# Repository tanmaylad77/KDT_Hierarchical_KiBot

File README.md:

<h1 align="center">LE_BMS_A_V2</h1>

<p align="center" width="100%">
  
</p>

***

<p align="center">
  
&nbsp; &nbsp; &nbsp; &nbsp;
  
</p>

***

## SPECIFICATIONS

| Parameter | Value | 
| --- | --- |
| Dimensions | 80.0 × 80.0 mm |

***

## DIRECTORY STRUCTURE

    .
    ├─ Computations       # Misc calculations
    ├─ HTML               # HTML files for generated webpage
    ├─ Images             # Pictures and renders
    │
    ├─ kibot_resources    # External resources for KiBot
    │  ├─ colors          # Color theme for KiCad
    │  ├─ fonts           # Fonts used in the project
    │  ├─ scripts         # External scripts used with KiBot
    │  └─ templates       # Templates for KiBot generated reports
    │
    ├─ kibot_yaml         # KiBot YAML config files
    ├─ KiRI               # KiRI (PCB diff viewer) files
    │
    ├─ lib                # KiCad footprint and symbol libraries
    │  ├─ 3d_models       # Component 3D models
    │  ├─ lib_fp          # Footprint libraries
    │  └─ lib_sym         # Symbol libraries
    │
    ├─ Logos              # Logos
    │
    ├─ Manufacturing      # Assembly and fabrication documents
    │  ├─ Assembly        # Assembly documents (BoM, pos, notes)
    │  │
    │  └─ Fabrication     # Fabrication documents (ZIP, notes)
    │     ├─ Drill Tables # CSV drill tables
    │     └─ Gerbers      # Gerbers
    │
    ├─ Report             # Reports for ERC/DRC
    ├─ Schematic          # PDF of schematic
    ├─ Templates          # Title block templates
    ├─ Testing
    │  └─ Testpoints      # Testpoints tables      
    │
    └─ Variants           # Outputs for assembly variants

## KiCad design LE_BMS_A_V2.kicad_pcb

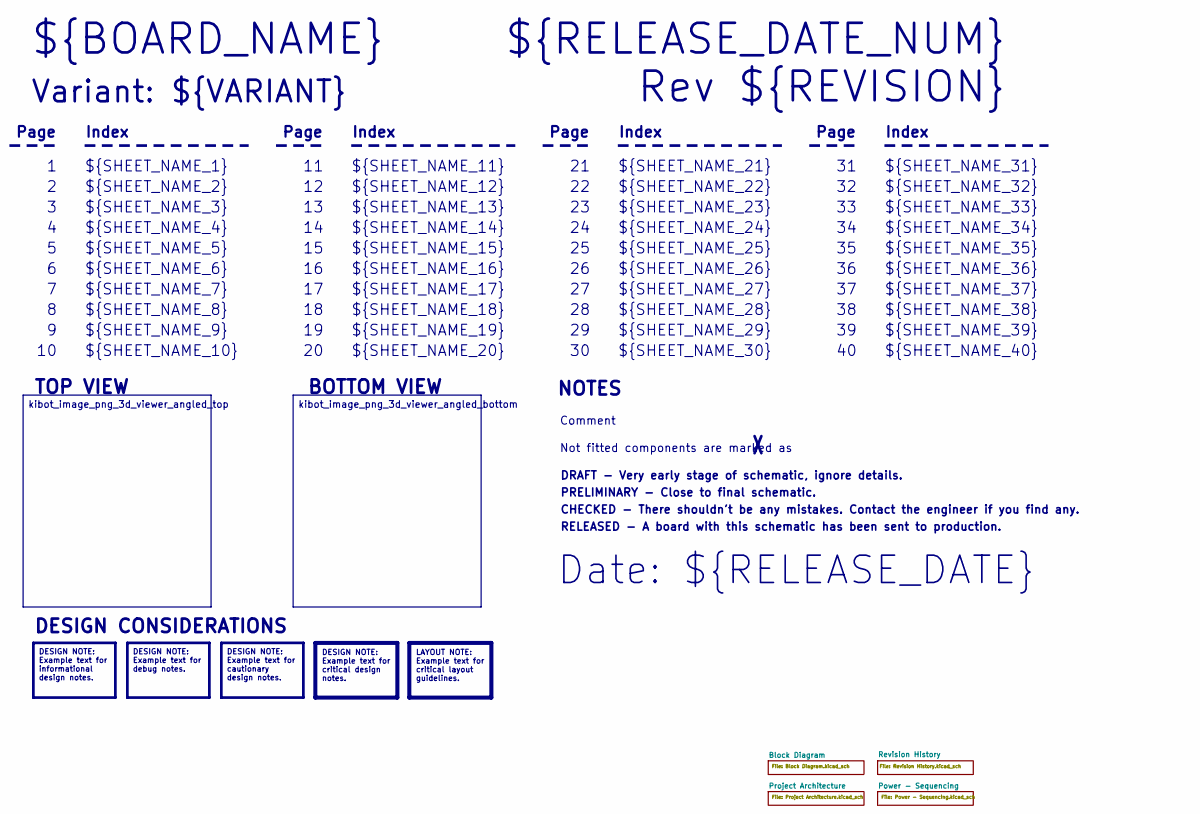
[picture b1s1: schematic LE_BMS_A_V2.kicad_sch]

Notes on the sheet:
Variant: ${VARIANT}
RELEASED - A board with this schematic has been sent to production.
${SHEET_NAME_24}
Index
Page
PRELIMINARY - Close to final schematic.
${SHEET_NAME_22}
DRAFT - Very early stage of schematic, ignore details.
${SHEET_NAME_12}
${SHEET_NAME_8}
${SHEET_NAME_2}
${SHEET_NAME_5}
${SHEET_NAME_20}
${SHEET_NAME_23}
${RELEASE_DATE_NUM}
${SHEET_NAME_35}
Not fitted components are marked as
${SHEET_NAME_11}
${SHEET_NAME_6}
${SHEET_NAME_37}
${SHEET_NAME_26}
${SHEET_NAME_36}
Rev ${REVISION}
${SHEET_NAME_15}
CHECKED - There shouldn't be any mistakes. Contact the engineer if you find any.
BOTTOM VIEW
${SHEET_NAME_14}
${SHEET_NAME_21}
${SHEET_NAME_17}
${SHEET_NAME_18}
Date: ${RELEASE_DATE}
${SHEET_NAME_7}
${SHEET_NAME_31}
${BOARD_NAME}
NOTES
${SHEET_NAME_40}
${SHEET_NAME_39}
${SHEET_NAME_32}
${SHEET_NAME_1}
${SHEET_NAME_9}

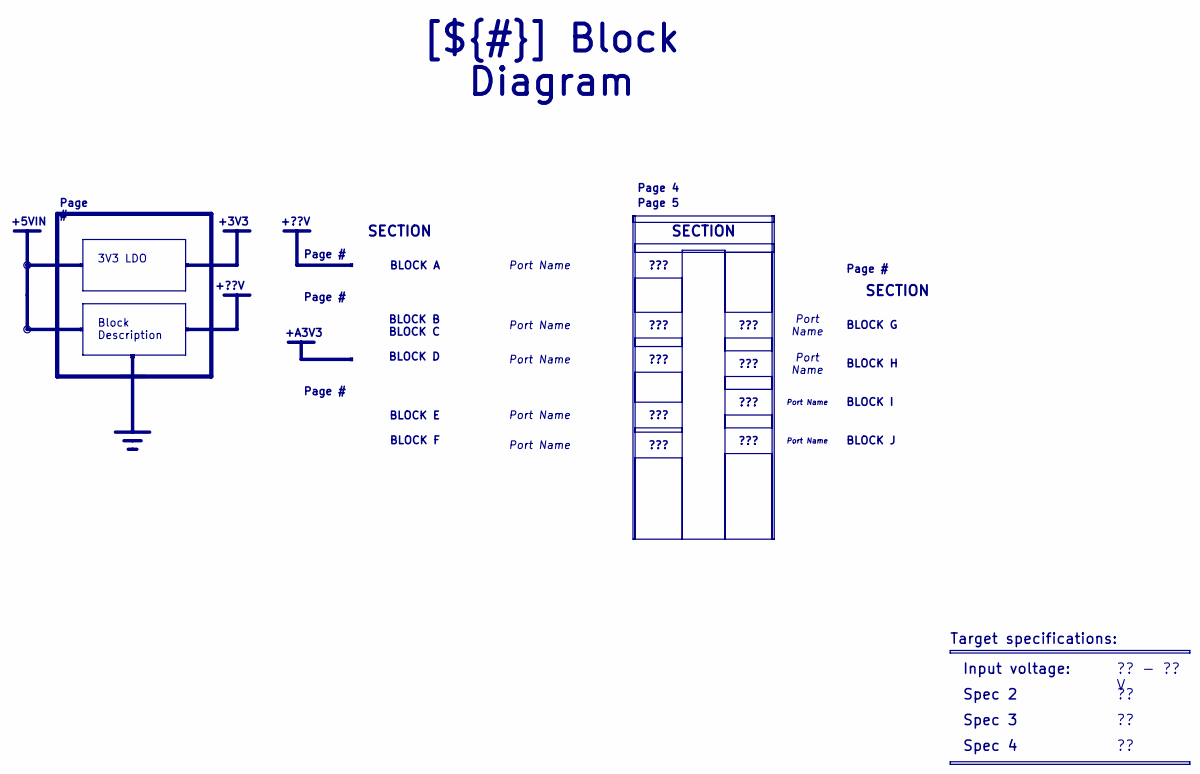
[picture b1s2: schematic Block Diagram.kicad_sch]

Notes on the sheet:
+5VIN
+??V
+A3V3
+3V3
SECTION
Spec 4
BLOCK H
BLOCK B BLOCK C BLOCK D
BLOCK I
?? - ?? V
3V3 LDO
???
Port Name
BLOCK G
Page #
Page 4
[${#}] ${TITLE}
Input voltage:
Target specifications:
Spec 3
Spec 2
Block Description
BLOCK A
BLOCK E BLOCK F
BLOCK J
Page 5

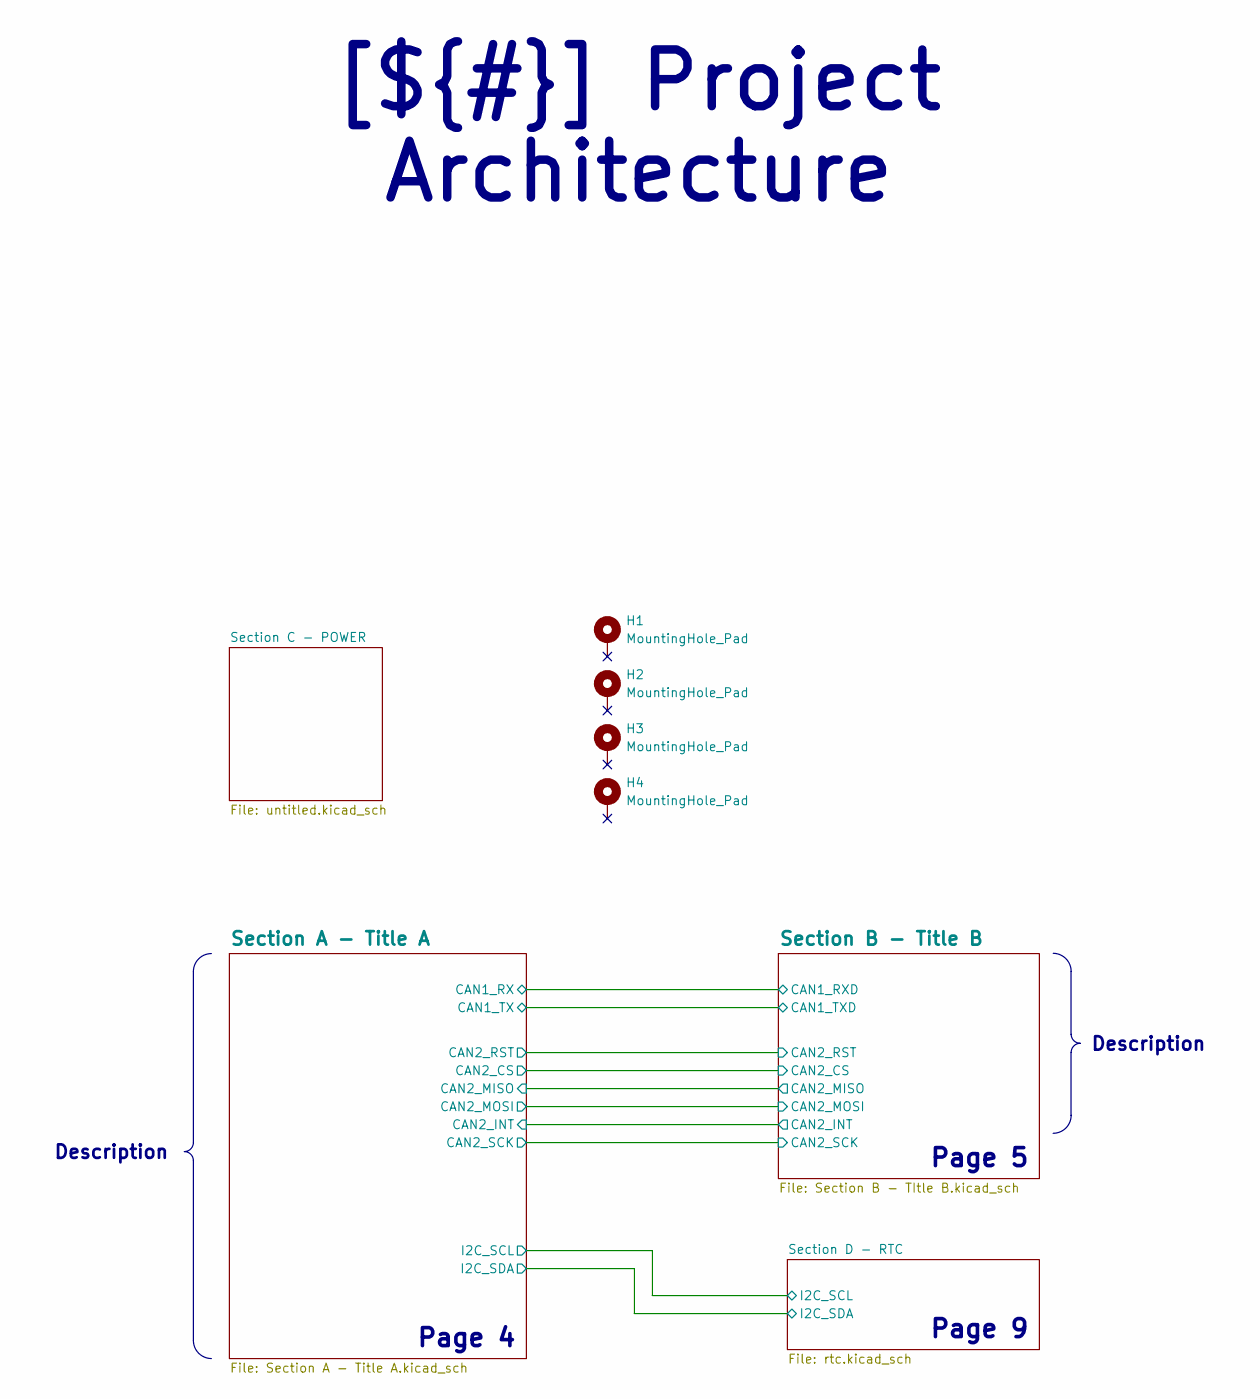
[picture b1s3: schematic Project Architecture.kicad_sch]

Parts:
H1, H2, H3, H4: MountingHole_Pad; MountingHole_3.2mm_M3_DIN965_Pad

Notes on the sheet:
Page 9
Page 5
Page 4
Description
[${#}] ${TITLE}

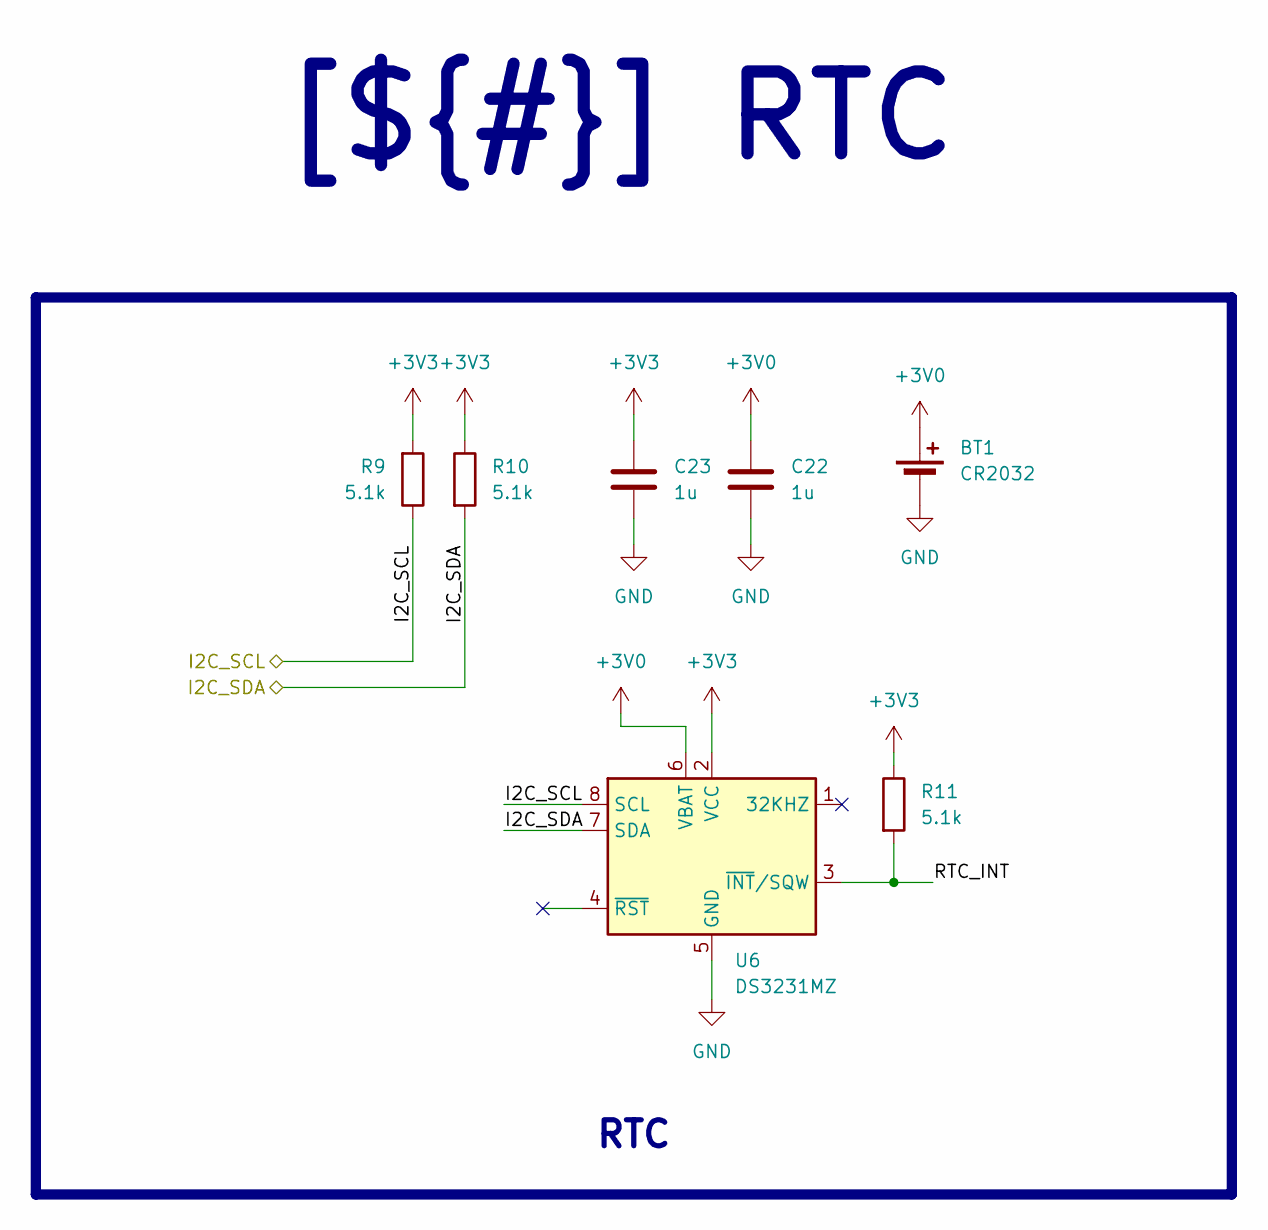
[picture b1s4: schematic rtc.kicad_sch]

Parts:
BT1: CR2032; BatteryHolder_MYOUNG_BS-07-A1BJ001_CR2032
C22, C23: 1u; C_0603_1608Metric_Pad1.08x0.95mm_HandSolder
R9, R10, R11: 5.1k; R_0603_1608Metric_Pad0.98x0.95mm_HandSolder
U6: DS3231MZ; SOIC-8_3.9x4.9mm_P1.27mm

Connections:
+3V0: BT1.1 (+), C22.1, U6.6 (VBAT)
+3V3: C23.1, R9.2, R10.1, R11.1, U6.2 (VCC); also elsewhere on the board
/Project Architecture/Section D - RTC/I2C_SCL: R9.1, U6.8 (SCL); also elsewhere on the board
/Project Architecture/Section D - RTC/I2C_SDA: R10.2, U6.7 (SDA); also elsewhere on the board
/Project Architecture/Section D - RTC/RTC_INT: R11.2, U6.3 (~INT/SQW)
GND: BT1.2 (-), C22.2, C23.2, U6.5 (GND); also elsewhere on the board

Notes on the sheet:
[${#}] ${TITLE}
RTC

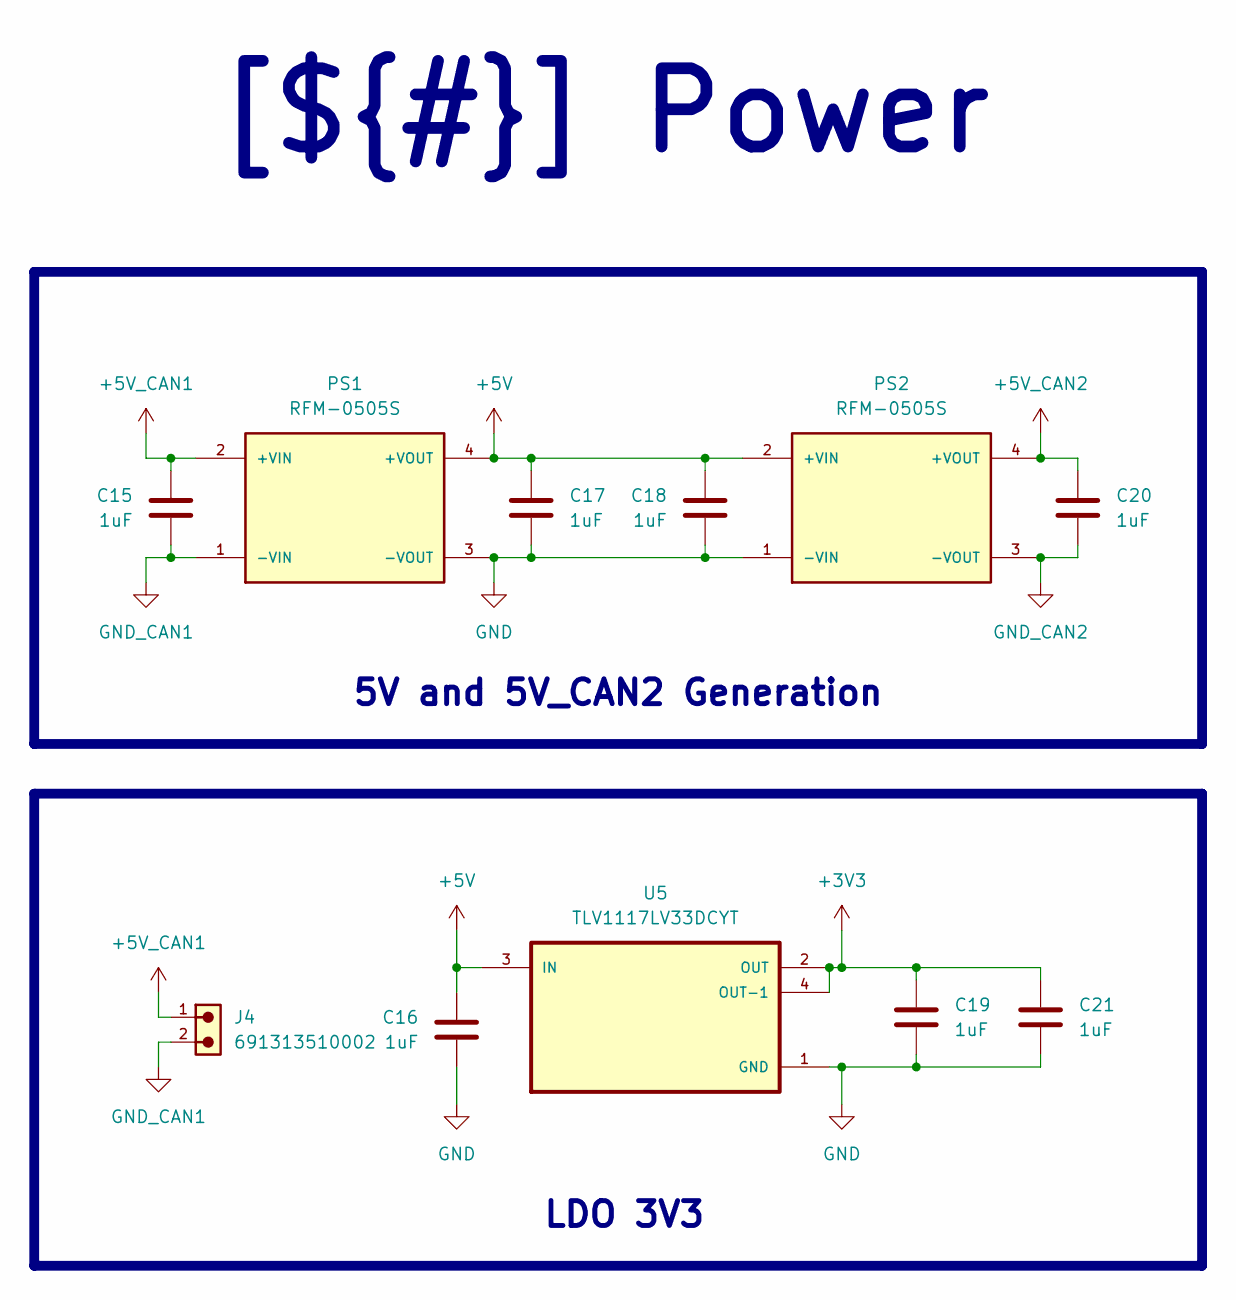
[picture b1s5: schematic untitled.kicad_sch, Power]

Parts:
C15, C16, C17, C18, C19, C20, C21: 1uF; C_0603_1608Metric_Pad1.08x0.95mm_HandSolder
J4: 691313510002
PS1, PS2: RFM-0505S; CONV_RFM-0505S; PARTREV 0
U5: TLV1117LV33DCYT; SOT230P700X180-4N

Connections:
+3V3: C19.1, C21.1, U5.2 (OUT), U5.4 (OUT-1); also elsewhere on the board
+5V: C16.1, C17.1, C18.1, PS1.4 (+VOUT), PS2.2 (+VIN), U5.3 (IN); also elsewhere on the board
+5V_CAN1: C15.1, J4.1, PS1.2 (+VIN); also elsewhere on the board
+5V_CAN2: C20.1, PS2.4 (+VOUT); also elsewhere on the board
GND: C16.2, C17.2, C18.2, C19.2, C21.2, PS1.3 (-VOUT), PS2.1 (-VIN), U5.1 (GND); also elsewhere on the board
GND_CAN1: C15.2, J4.2, PS1.1 (-VIN); also elsewhere on the board
GND_CAN2: C20.2, PS2.3 (-VOUT); also elsewhere on the board

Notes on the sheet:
[${#}] ${TITLE}
5V and 5V_CAN2 Generation
LDO 3V3

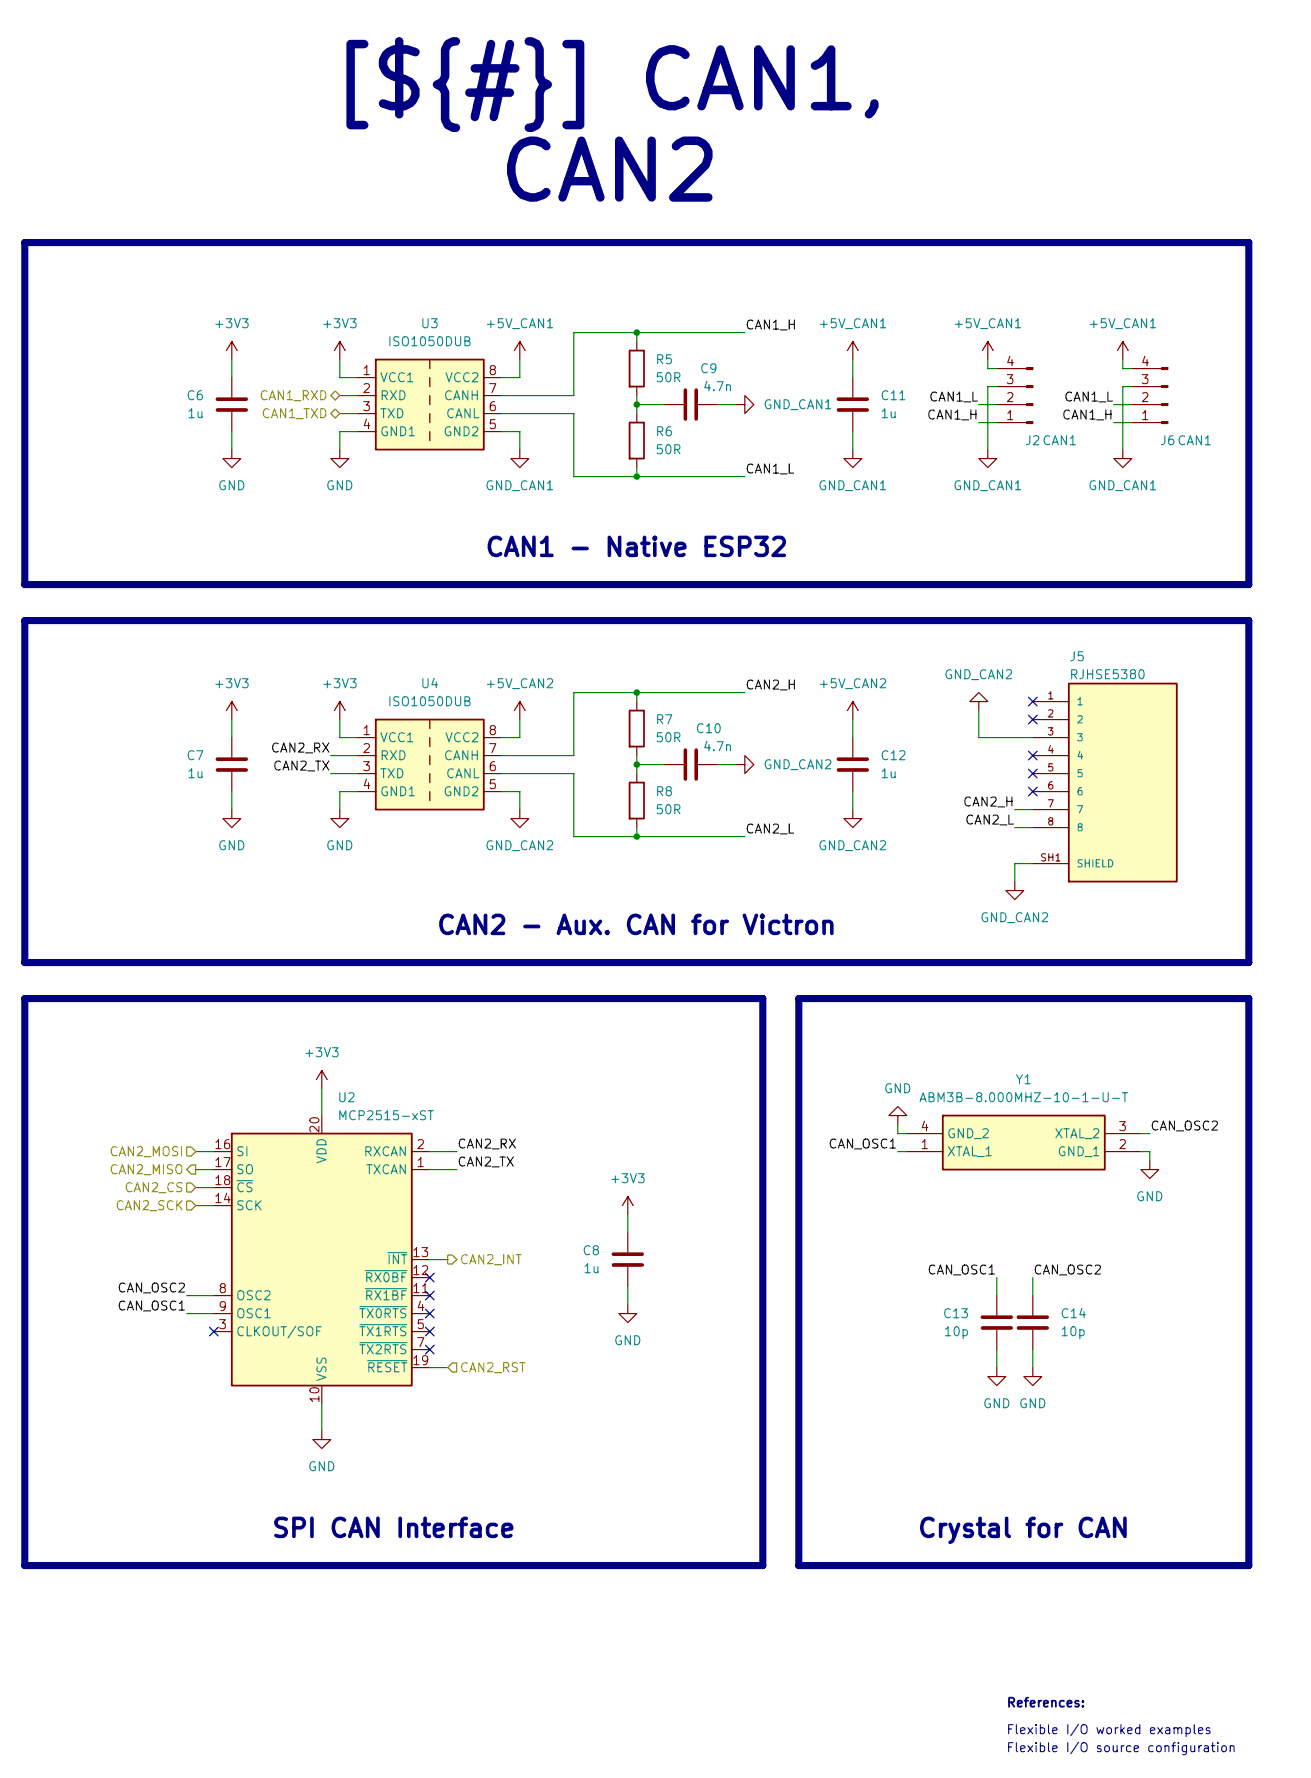
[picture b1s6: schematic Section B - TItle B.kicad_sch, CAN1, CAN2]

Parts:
C6, C7, C8, C11, C12: 1u; C_0603_1608Metric_Pad1.08x0.95mm_HandSolder
C9, C10: 4.7n; C_0603_1608Metric_Pad1.08x0.95mm_HandSolder
C13, C14: 10p; C_0603_1608Metric_Pad1.08x0.95mm_HandSolder
J2, J6: CAN1; JST_XH_S4B-XH-A_1x04_P2.50mm_Horizontal
J5: RJHSE5380; AMPHENOL_RJHSE5380; PARTREV B
R5, R6, R7, R8: 50R; R_0603_1608Metric_Pad0.98x0.95mm_HandSolder
U2: MCP2515-xST; TSSOP-20_4.4x6.5mm_P0.65mm
U3, U4: ISO1050DUB; SOP-8_6.62x9.15mm_P2.54mm
Y1: ABM3B-8.000MHZ-10-1-U-T; ABM3B; Mouser Part Number 815-ABM3B8MHZ101UT

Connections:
+3V3: C6.1, C7.1, C8.1, U2.20 (VDD), U3.1 (VCC1), U4.1 (VCC1); also elsewhere on the board
+5V_CAN1: C11.1, J2.4, J6.4, U3.8 (VCC2); also elsewhere on the board
+5V_CAN2: C12.1, U4.8 (VCC2); also elsewhere on the board
/Project Architecture/Section A - Title A/CAN1_RX: U3.2 (RXD); also elsewhere on the board
/Project Architecture/Section A - Title A/CAN1_TX: U3.3 (TXD); also elsewhere on the board
/Project Architecture/Section A - Title A/CAN2_CS: U2.18 (~CS); also elsewhere on the board
/Project Architecture/Section A - Title A/CAN2_INT: U2.13 (~INT); also elsewhere on the board
/Project Architecture/Section A - Title A/CAN2_MISO: U2.17 (SO); also elsewhere on the board
/Project Architecture/Section A - Title A/CAN2_MOSI: U2.16 (SI); also elsewhere on the board
/Project Architecture/Section A - Title A/CAN2_RST: U2.19 (~RESET); also elsewhere on the board
/Project Architecture/Section A - Title A/CAN2_SCK: U2.14 (SCK); also elsewhere on the board
/Project Architecture/Section B - Title B/CAN1_H: J2.1, J6.1, R5.1, U3.7 (CANH)
/Project Architecture/Section B - Title B/CAN1_L: J2.2, J6.2, R6.2, U3.6 (CANL)
/Project Architecture/Section B - Title B/CAN2_H: J5.7, R7.1, U4.7 (CANH)
/Project Architecture/Section B - Title B/CAN2_L: J5.8, R8.2, U4.6 (CANL)
/Project Architecture/Section B - Title B/CAN2_RX: U2.2 (RXCAN), U4.2 (RXD)
/Project Architecture/Section B - Title B/CAN2_TX: U2.1 (TXCAN), U4.3 (TXD)
/Project Architecture/Section B - Title B/CAN_OSC1: C13.1, U2.9 (OSC1), Y1.1 (XTAL_1)
/Project Architecture/Section B - Title B/CAN_OSC2: C14.1, U2.8 (OSC2), Y1.3 (XTAL_2)
GND: C6.2, C7.2, C8.2, C13.2, C14.2, U2.10 (VSS), U3.4 (GND1), U4.4 (GND1), Y1.2 (GND_1), Y1.4 (GND_2); also elsewhere on the board
GND_CAN1: C9.2, C11.2, J2.3, J6.3, U3.5 (GND2); also elsewhere on the board
GND_CAN2: C10.2, C12.2, J5.3, J5.SH1 (SHIELD), J5.SH2 (SHIELD), U4.5 (GND2); also elsewhere on the board
unnamed: C9.1, R5.2, R6.1
unnamed: C10.1, R7.2, R8.1

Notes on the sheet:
Flexible I/O worked examples
References:
Flexible I/O source configuration
[${#}] ${TITLE}
CAN1 - Native ESP32
CAN2 - Aux. CAN for Victron
Crystal for CAN
SPI CAN Interface

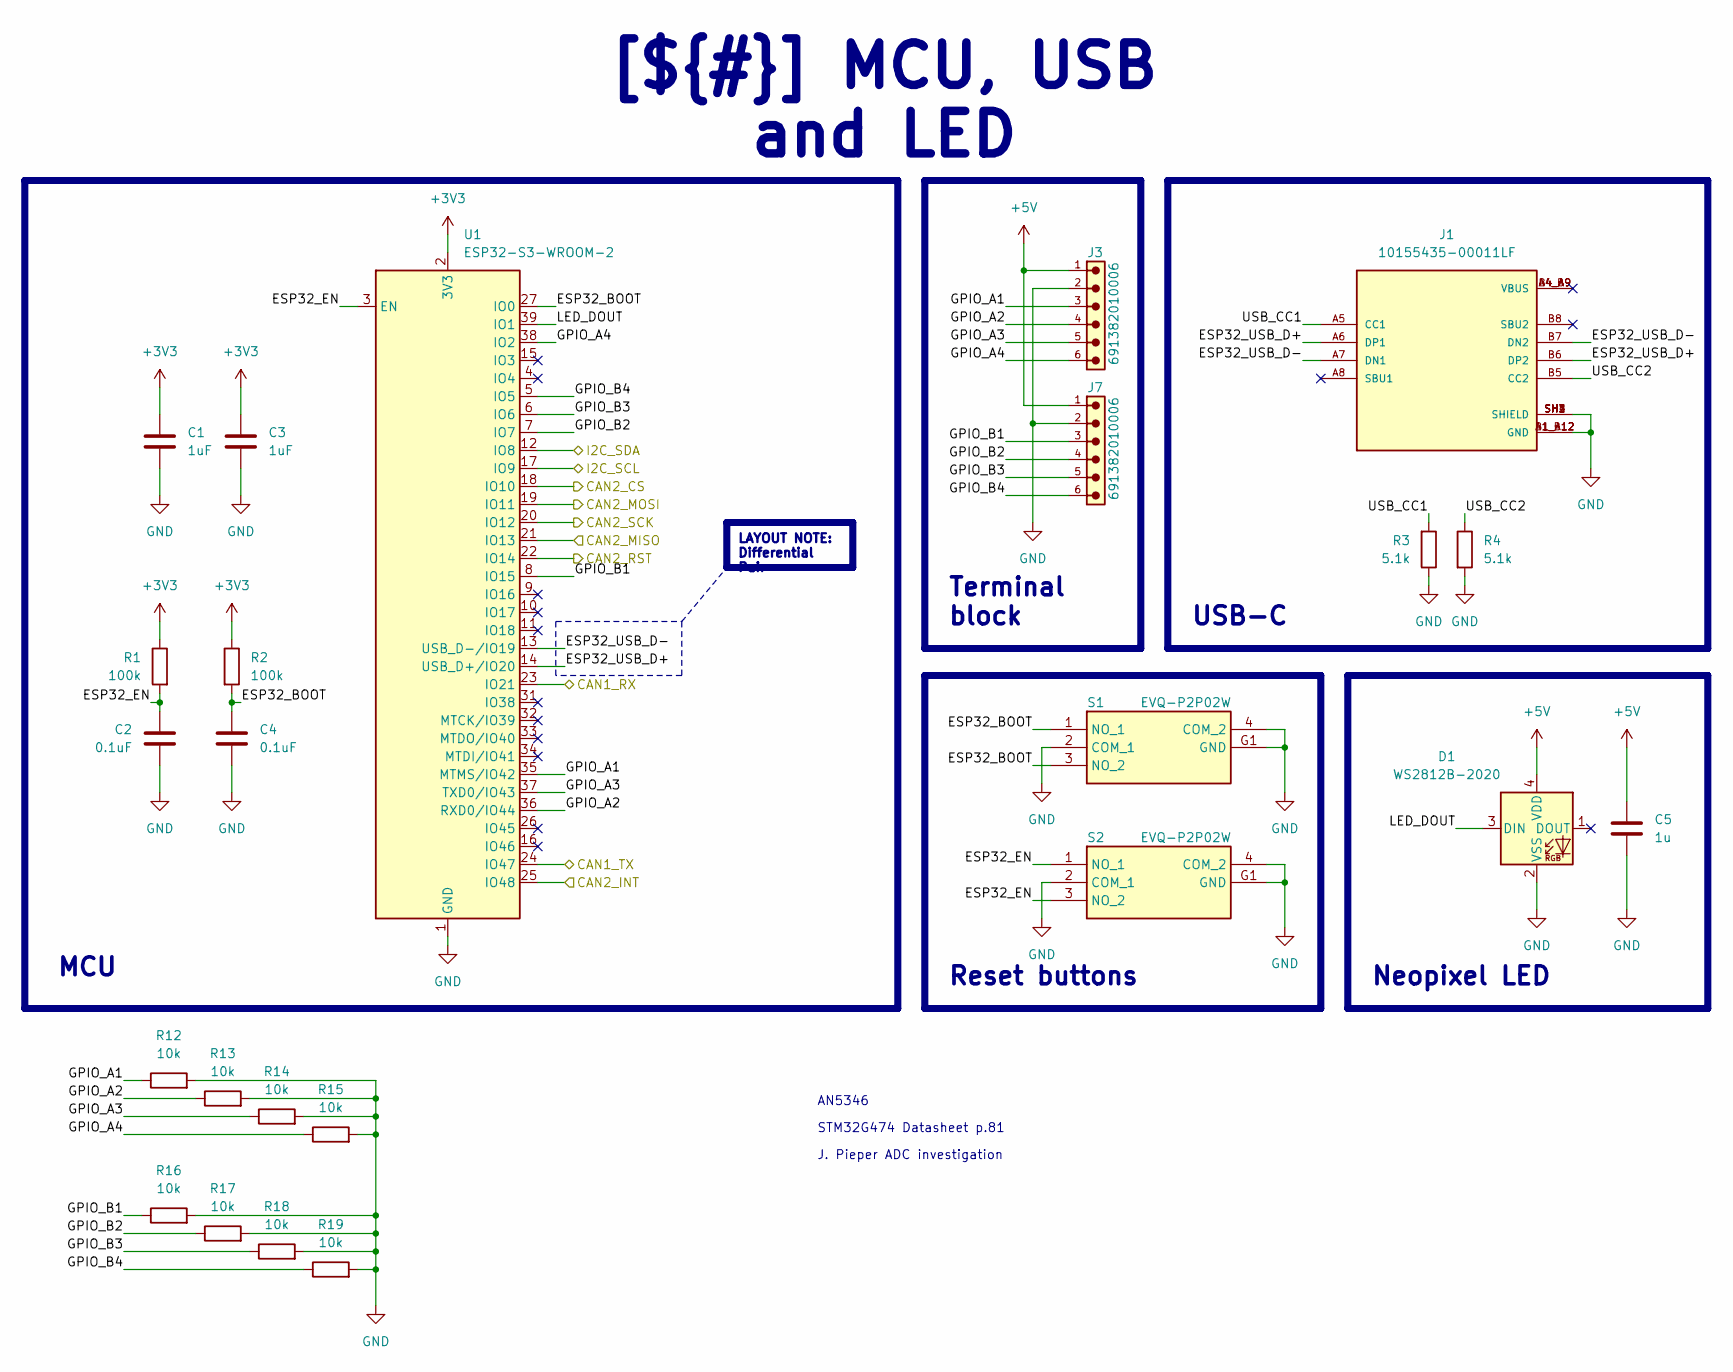
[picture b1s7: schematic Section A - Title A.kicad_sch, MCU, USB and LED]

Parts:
C1, C3: 1uF; C_0603_1608Metric_Pad1.08x0.95mm_HandSolder
C2, C4: 0.1uF; C_0603_1608Metric_Pad1.08x0.95mm_HandSolder
C5: 1u; C_0603_1608Metric_Pad1.08x0.95mm_HandSolder
D1: WS2812B-2020; LED_WS2812B-2020_PLCC4_2.0x2.0mm
J1: 10155435-00011LF; AMPHENOL_10155435-00011LF; PARTREV C
J3, J7: 691382010006
R1, R2: 100k; R_0603_1608Metric_Pad0.98x0.95mm_HandSolder
R3, R4: 5.1k; R_0603_1608Metric_Pad0.98x0.95mm_HandSolder
R12, R13, R14, R15, R16, R17, R18, R19: 10k; R_0603_1608Metric_Pad0.98x0.95mm_HandSolder
S1, S2: EVQ-P2P02W; EVQP2P02W; Mouser Part Number 667-EVQ-P2P02W
U1: ESP32-S3-WROOM-2

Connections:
+3V3: C1.1, C3.1, R1.1, R2.1, U1.2 (3V3); also elsewhere on the board
+5V: C5.1, D1.4 (VDD), J3.1, J7.1; also elsewhere on the board
/Project Architecture/Section A - Title A/CAN1_RX: U1.23 (IO21); also elsewhere on the board
/Project Architecture/Section A - Title A/CAN1_TX: U1.24 (IO47); also elsewhere on the board
/Project Architecture/Section A - Title A/CAN2_CS: U1.18 (IO10); also elsewhere on the board
/Project Architecture/Section A - Title A/CAN2_INT: U1.25 (IO48); also elsewhere on the board
/Project Architecture/Section A - Title A/CAN2_MISO: U1.21 (IO13); also elsewhere on the board
/Project Architecture/Section A - Title A/CAN2_MOSI: U1.19 (IO11); also elsewhere on the board
/Project Architecture/Section A - Title A/CAN2_RST: U1.22 (IO14); also elsewhere on the board
/Project Architecture/Section A - Title A/CAN2_SCK: U1.20 (IO12); also elsewhere on the board
/Project Architecture/Section A - Title A/ESP32_BOOT: C4.1, R2.2, S1.1 (NO_1), S1.3 (NO_2), U1.27 (IO0)
/Project Architecture/Section A - Title A/ESP32_EN: C2.1, R1.2, S2.1 (NO_1), S2.3 (NO_2), U1.3 (EN)
/Project Architecture/Section A - Title A/ESP32_USB_D+: J1.A6 (DP1), J1.B6 (DP2), U1.14 (USB_D+/IO20)
/Project Architecture/Section A - Title A/ESP32_USB_D-: J1.A7 (DN1), J1.B7 (DN2), U1.13 (USB_D-/IO19)
/Project Architecture/Section A - Title A/GPIO_A1: J3.3, R12.1, U1.35 (MTMS/IO42)
/Project Architecture/Section A - Title A/GPIO_A2: J3.4, R13.1, U1.36 (RXD0/IO44)
/Project Architecture/Section A - Title A/GPIO_A3: J3.5, R14.1, U1.37 (TXD0/IO43)
/Project Architecture/Section A - Title A/GPIO_A4: J3.6, R15.1, U1.38 (IO2)
/Project Architecture/Section A - Title A/GPIO_B1: J7.3, R16.1, U1.8 (IO15)
/Project Architecture/Section A - Title A/GPIO_B2: J7.4, R17.1, U1.7 (IO7)
/Project Architecture/Section A - Title A/GPIO_B3: J7.5, R18.1, U1.6 (IO6)
/Project Architecture/Section A - Title A/GPIO_B4: J7.6, R19.1, U1.5 (IO5)
/Project Architecture/Section A - Title A/LED_DOUT: D1.3 (DIN), U1.39 (IO1)
/Project Architecture/Section A - Title A/USB_CC1: J1.A5 (CC1), R3.2
/Project Architecture/Section A - Title A/USB_CC2: J1.B5 (CC2), R4.1
/Project Architecture/Section D - RTC/I2C_SCL: U1.17 (IO9); also elsewhere on the board
/Project Architecture/Section D - RTC/I2C_SDA: U1.12 (IO8); also elsewhere on the board
GND: C1.2, C2.2, C3.2, C4.2, C5.2, D1.2 (VSS), J1.A1_B12 (GND), J1.B1_A12 (GND), J1.SH1 (SHIELD), J1.SH2 (SHIELD), J1.SH3 (SHIELD), J1.SH4 (SHIELD), J3.2, J7.2, R3.1, R4.2, R12.2, R13.2, R14.2, R15.2, R16.2, R17.2, R18.2, R19.2, S1.2 (COM_1), S1.4 (COM_2), S1.G1 (GND), S2.2 (COM_1), S2.4 (COM_2), S2.G1 (GND), U1.1 (GND), U1.40 (GND), U1.41 (GND); also elsewhere on the board

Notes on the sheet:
J. Pieper ADC investigation
STM32G474 Datasheet p.81
AN5346
USB-C
Reset buttons
Neopixel LED
LAYOUT NOTE: Differential Pair
Terminal block
[${#}] ${TITLE}
MCU

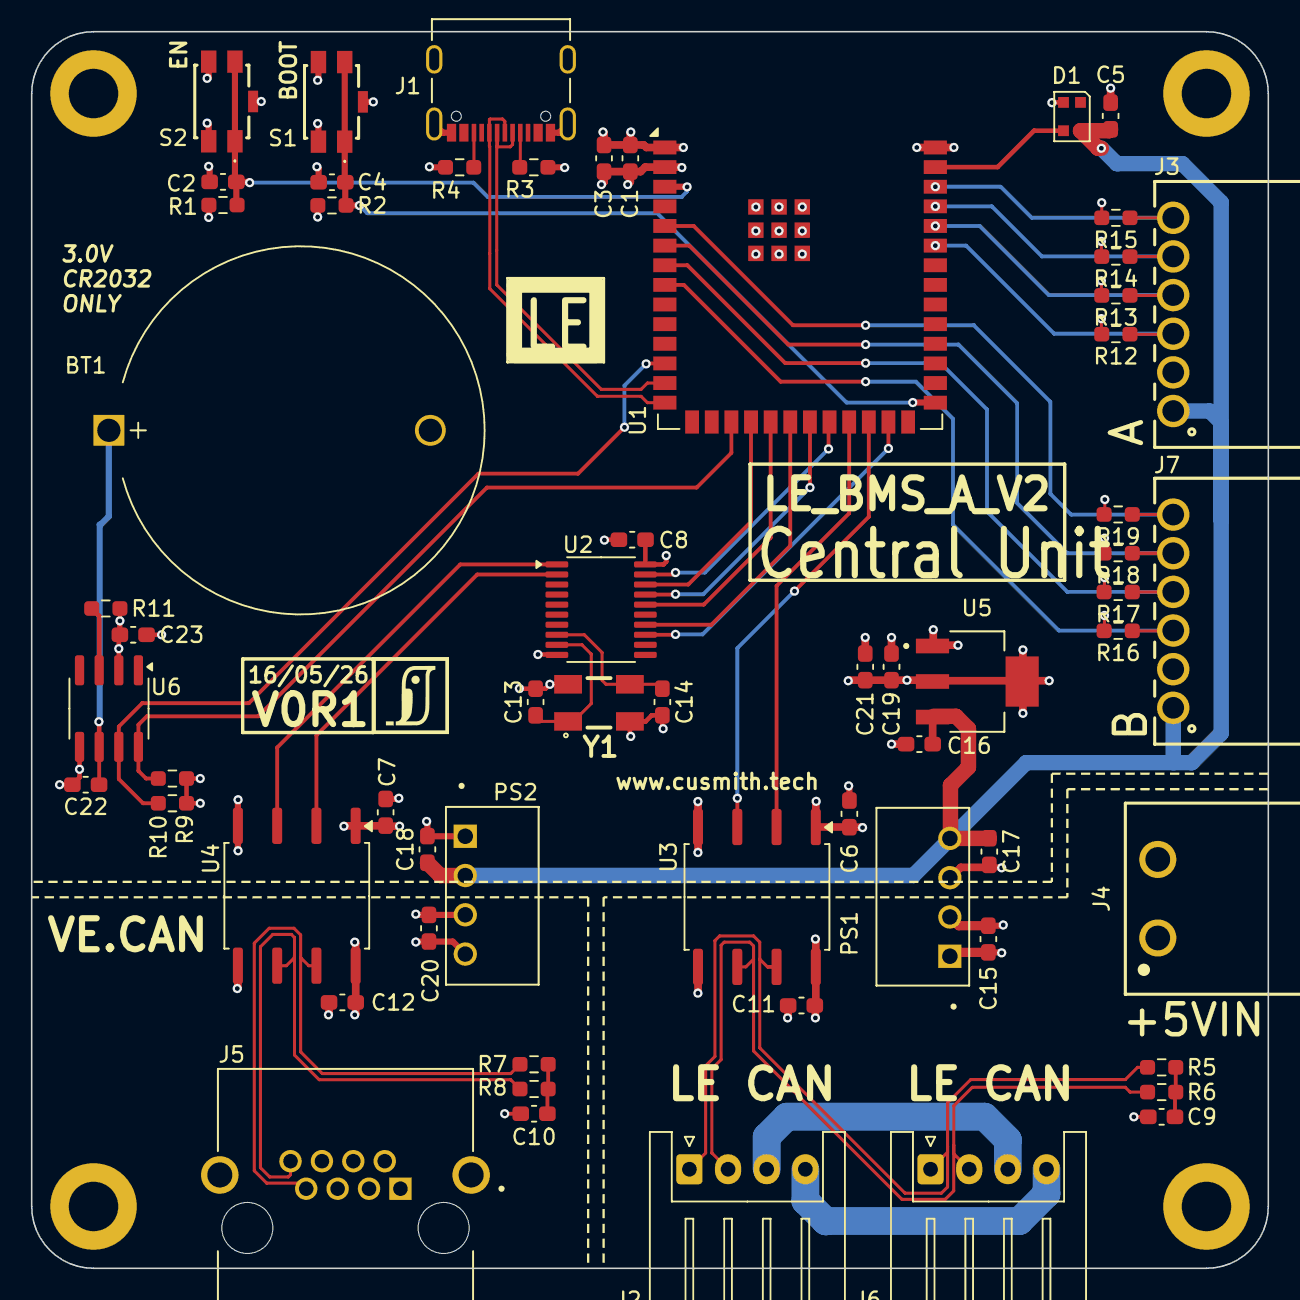
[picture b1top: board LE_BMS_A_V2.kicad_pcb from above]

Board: 4 copper layers, 80.0 x 80.0 mm, 66 parts (0 on the bottom side), 44 nets.

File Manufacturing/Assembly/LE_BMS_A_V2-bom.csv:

Row,Quantity Per PCB,References,Value,Datasheet,Footprint,Description,Manufacturer,Manufacturer Part Number,Supplier Part Number
1,1,BT1,CR2032,~,BatteryHolder_MYOUNG_BS-07-A1BJ001_CR2032,Single-cell battery,,,
2,2,C13 C14,10p,~,C_0603_1608Metric_Pad1.08x0.95mm_HandSolder,Unpolarized capacitor,,,
3,2,C9 C10,4.7n,~,C_0603_1608Metric_Pad1.08x0.95mm_HandSolder,Unpolarized capacitor,,,
4,2,C2 C4,0.1uF,~,C_0603_1608Metric_Pad1.08x0.95mm_HandSolder,Unpolarized capacitor,,,
5,17,C1 C3 C5 C6 C7 C8 C11 C12 C15 C16 C17 C18 C19 C20 C21 C22 C23,1uF,~,C_0603_1608Metric_Pad1.08x0.95mm_HandSolder,Unpolarized capacitor,,,
6,1,D1,WS2812B-2020,https://cdn-shop.adafruit.com/product-files/4684/4684_WS2812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,LED_WS2812B-2020_PLCC4_2.0x2.0mm,"RGB LED with integrated controller, 2.0 x 2.0 mm, 12 mA",,,
7,1,J1,10155435-00011LF,,AMPHENOL_10155435-00011LF,,Amphenol,,
8,1,J4,691313510002,,691313510002,,,,
9,2,J3 J7,691382010006,,691382010006,,,,
10,2,J2 J6,CAN1,~,JST_XH_S4B-XH-A_1x04_P2.50mm_Horizontal,"Generic connector, single row, 01x04, script generated",,,
11,1,J5,RJHSE5380,,AMPHENOL_RJHSE5380,,Amphenol,,
12,2,PS1 PS2,RFM-0505S,,CONV_RFM-0505S,,Recom,,
13,4,R5 R6 R7 R8,50R,~,R_0603_1608Metric_Pad0.98x0.95mm_HandSolder,Resistor,,,
14,5,R3 R4 R9 R10 R11,5.1k,~,R_0603_1608Metric_Pad0.98x0.95mm_HandSolder,Resistor,,,
15,2,R1 R2,100k,~,R_0603_1608Metric_Pad0.98x0.95mm_HandSolder,Resistor,,,
16,2,S1 S2,EVQ-P2P02W,https://www.digikey.com/en/products/detail/panasonic-electro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,EVQP2P02W,Tactile Switches 4.7x3.5mm SMD Light Touch Switch,,,
17,1,U6,DS3231MZ,http://datasheets.maximintegrated.com/en/ds/DS3231M.pdf,SOIC-8_3.9x4.9mm_P1.27mm,"±5ppm, I2C Real-Time Clock SOIC-8",,,
18,1,U1,ESP32-S3-WROOM-2,https://www.espressif.com/sites/default/files/documentation/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,ESP32-S3-WROOM-2,"RF Module, 2.4 GHz, Wi­-Fi, Bluetooth, BLE, ESP32­-S3R8V",,,
19,2,U3 U4,ISO1050DUB,http://www.ti.com/lit/ds/symlink/iso1050.pdf,SOP-8_6.62x9.15mm_P2.54mm,"Isolated CAN Transceiver, SOP-8",,,
20,1,U2,MCP2515-xST,http://ww1.microchip.com/downloads/en/DeviceDoc/21801e.pdf,TSSOP-20_4.4x6.5mm_P0.65mm,"Stand-Alone CAN Controller with SPI Interface, TSSOP-20",,,
21,1,U5,TLV1117LV33DCYT,,SOT230P700X180-4N,,,,
22,1,Y1,ABM3B-8.000MHZ-10-1-U-T,https://abracon.com/Resonators/abm3b.pdf,ABM3B,"8 MHz +/-10ppm Crystal 10pF 200 Ohms 4-SMD, No Lead",,,

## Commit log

2026-05-16 Initial commit: Moved over previous design and added isolation to CAN bus.
2026-05-16 Update Outputs
2026-05-16 Moved the PCB a bit.
2026-05-18 Finished most routing, final checks to be done
2026-05-25 Final Changes, Updated to Checked
2026-05-25 Retry with rules DRC ERC passing
2026-05-25 Increased Via Sizes to 0.3/0.6
2026-05-25 Gitignored things
2026-05-25 Added pulldowns on GPIOs
2026-05-25 Final Commit on this Version
2026-05-25 Added JLCPCB BoM for Assembly
2026-05-25 Update CHANGELOG
